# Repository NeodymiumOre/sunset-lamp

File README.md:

# SunsetLamp
Alarm clock simulating sunrise.

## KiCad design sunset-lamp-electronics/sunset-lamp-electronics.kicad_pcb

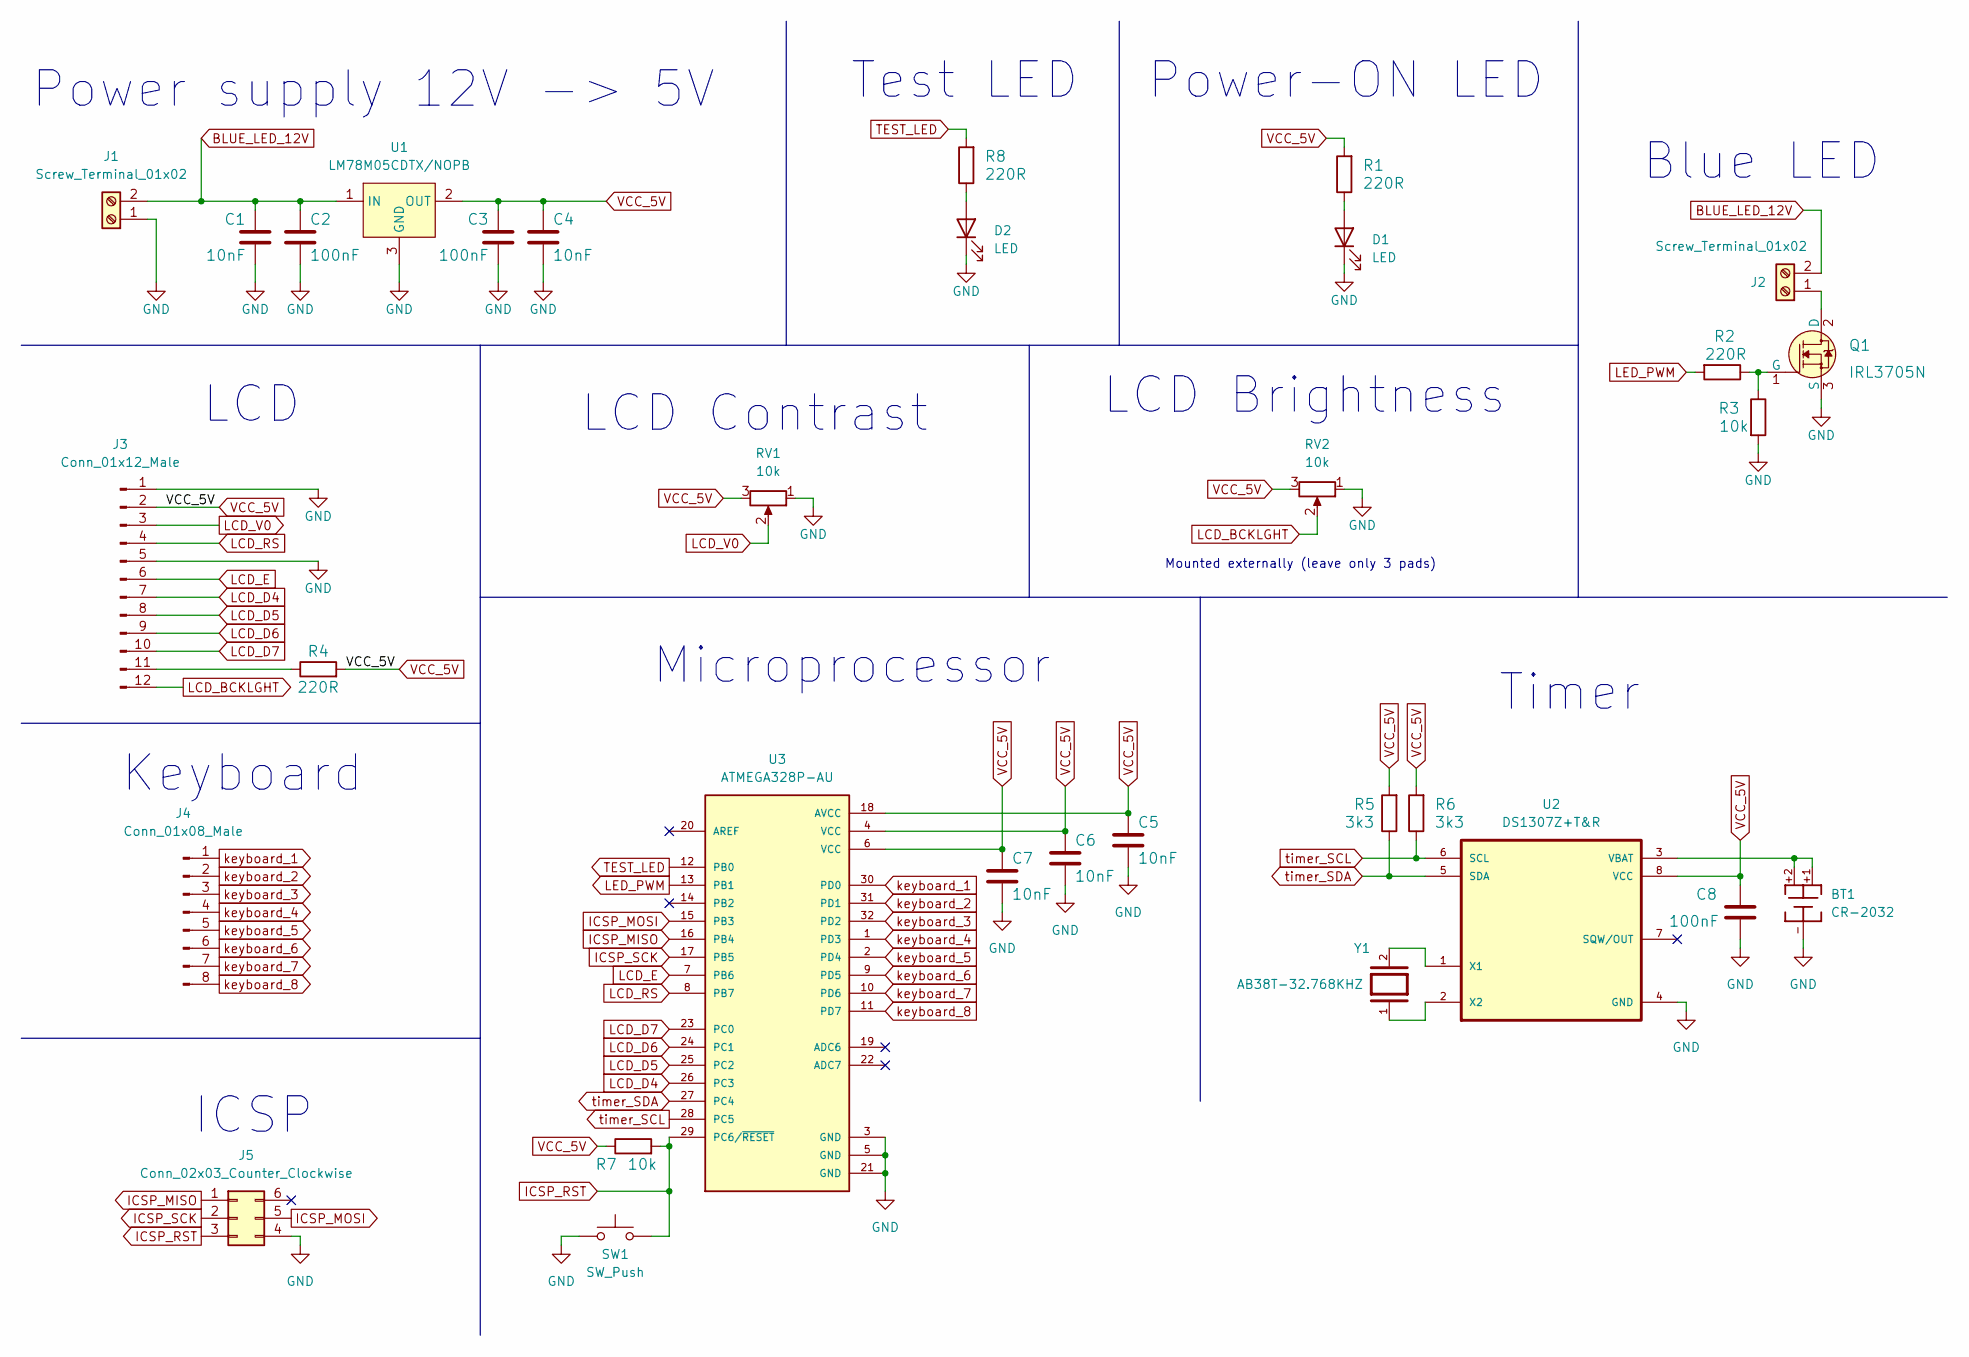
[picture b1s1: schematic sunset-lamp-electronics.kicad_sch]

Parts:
BT1: CR-2032; BAT_CR2032
C1, C4, C5, C6, C7: 10nF; 0402-cap
C2, C3, C8: 100nF; 0402-cap
D1, D2: LED; LED_0805_2012Metric_Pad1.15x1.40mm_HandSolder
J1, J2: Screw_Terminal_01x02; TerminalBlock_Altech_AK300-2_P5.00mm
J3: Conn_01x12_Male; PinHeader_1x12_P2.54mm_Vertical
J4: Conn_01x08_Male; PinHeader_1x08_P2.54mm_Vertical
J5: Conn_02x03_Counter_Clockwise; PinHeader_2x03_P2.54mm_Vertical
Q1: IRL3705N; TO-220
R1, R2, R4, R8: 220R; 0402-res
R3, R7: 10k; 0402-res
R5, R6: 3k3; 0402-res
RV1: 10k; TrimmPotentiometer
RV2: 10k; PinHeader_1x03_P2.54mm_Vertical
SW1: SW_Push; SW_PUSH_6mm_H5mm
U1: LM78M05CDTX/NOPB; TO-252-DPAK
U2: DS1307Z+T&R; SOIC-8
U3: ATMEGA328P-AU; TQFP-32
Y1: AB38T-32.768KHZ; XTAL_AB38T-32.768KHZ

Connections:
BLUE_LED_12V: C1.1, C2.1, J1.2, J2.2, U1.1 (IN)
GND: BT1.-, C1.2, C2.2, C3.2, C4.2, C5.2, C6.2, C7.2, C8.2, D1.1 (K), D2.1 (K), J1.1, J3.1, J3.5, J5.4, Q1.3 (S), R3.2, RV1.1, RV2.1, SW1.1, U1.3 (GND), U2.4 (GND), U3.3 (GND), U3.5 (GND), U3.21 (GND)
ICSP_MISO: J5.1, U3.16 (PB4)
ICSP_MOSI: J5.5, U3.15 (PB3)
ICSP_RST: J5.3, R7.2, SW1.2, U3.29 (PC6/~RESET)
ICSP_SCK: J5.2, U3.17 (PB5)
LCD_BCKLGHT: J3.12, RV2.2
LCD_D4: J3.7, U3.26 (PC3)
LCD_D5: J3.8, U3.25 (PC2)
LCD_D6: J3.9, U3.24 (PC1)
LCD_D7: J3.10, U3.23 (PC0)
LCD_E: J3.6, U3.7 (PB6)
LCD_RS: J3.4, U3.8 (PB7)
LCD_V0: J3.3, RV1.2
LED_PWM: R2.2, U3.13 (PB1)
unnamed: BT1.+1, BT1.+2, U2.3 (VBAT)
unnamed: D1.2 (A), R1.1
unnamed: D2.2 (A), R8.1
unnamed: J2.1, Q1.2 (D)
unnamed: J3.11, R4.1
unnamed: Q1.1 (G), R2.1, R3.1
unnamed: U2.1 (X1), Y1.2
unnamed: U2.2 (X2), Y1.1
TEST_LED: R8.2, U3.12 (PB0)
VCC_5V: C3.1, C4.1, C5.1, C6.1, C7.1, C8.1, J3.2, R1.2, R4.2, R5.2, R6.2, R7.1, RV1.3, RV2.3, U1.2 (OUT), U2.8 (VCC), U3.4 (VCC), U3.6 (VCC), U3.18 (AVCC)
keyboard_1: J4.1, U3.30 (PD0)
keyboard_2: J4.2, U3.31 (PD1)
keyboard_3: J4.3, U3.32 (PD2)
keyboard_4: J4.4, U3.1 (PD3)
keyboard_5: J4.5, U3.2 (PD4)
keyboard_6: J4.6, U3.9 (PD5)
keyboard_7: J4.7, U3.10 (PD6)
keyboard_8: J4.8, U3.11 (PD7)
timer_SCL: R6.1, U2.6 (SCL), U3.28 (PC5)
timer_SDA: R5.1, U2.5 (SDA), U3.27 (PC4)

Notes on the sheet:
LCD Brightness
Timer
Keyboard
LCD
LCD Contrast
ICSP
Test LED
Power supply 12V -> 5V
Power-ON LED
Microprocessor
Blue LED
Mounted externally (leave only 3 pads)

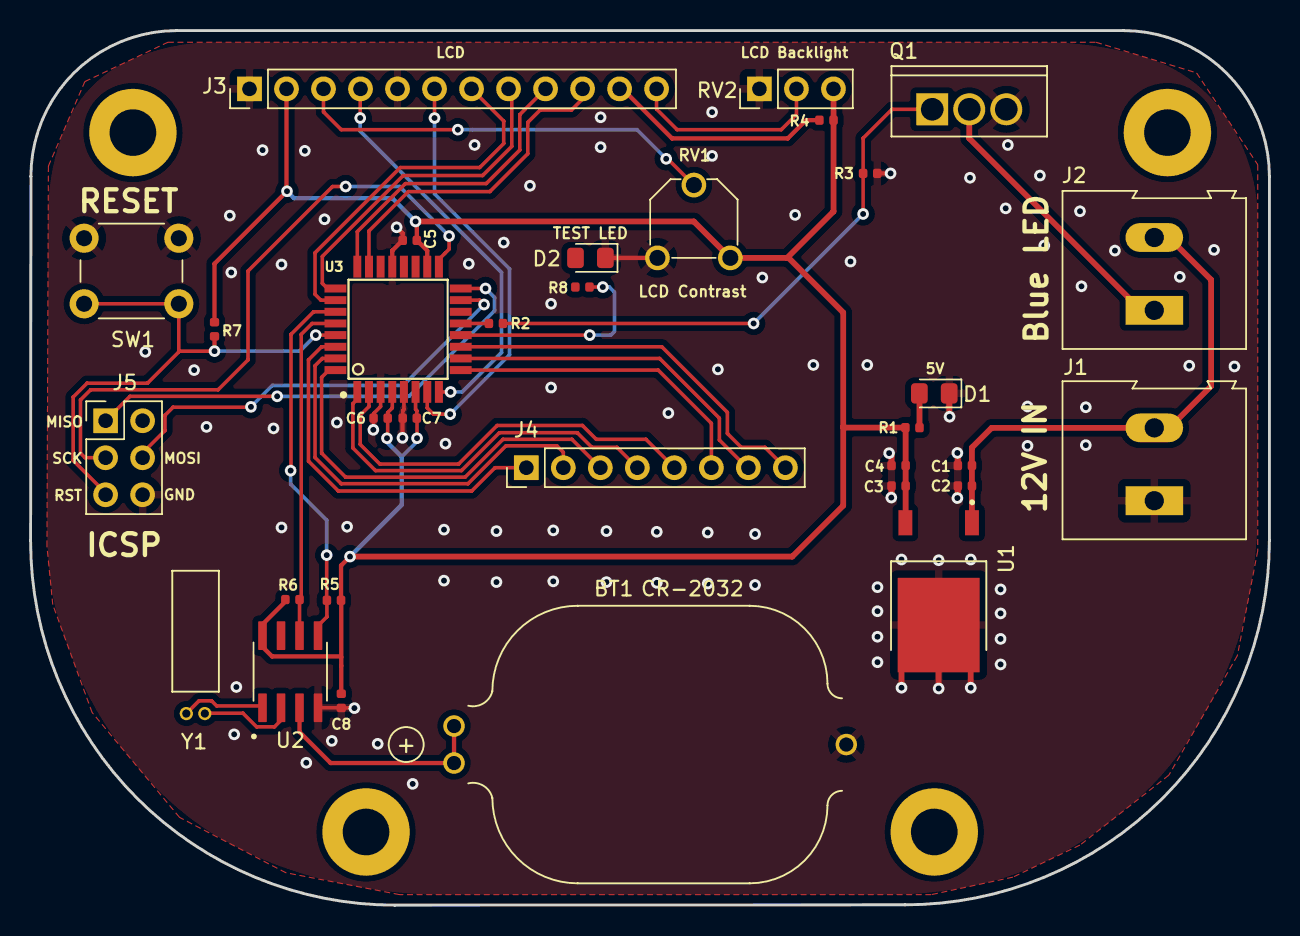
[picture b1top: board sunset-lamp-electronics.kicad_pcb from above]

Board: 2 copper layers, 85.0 x 60.0 mm, 32 parts (0 on the bottom side), 35 nets.

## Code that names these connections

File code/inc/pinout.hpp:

#include "pins_arduino.h"

// general pins
#define TEST_LED PIN_PB0
#define LED_PWM PIN_PB1
#define SOFT_RESET PIN_PC6

// LCD pins
#define LCD_E PIN_PB6
#define LCD_RS PIN_PB7
#define LCD_D7 PIN_PC0
#define LCD_D6 PIN_PC1
#define LCD_D5 PIN_PC2
#define LCD_D4 PIN_PC3

// KEYBOARD pins
#define ROW_1 PIN_PD0
#define ROW_2 PIN_PD1
#define ROW_3 PIN_PD2
#define ROW_4 PIN_PD3
#define COL_1 PIN_PD4
#define COL_2 PIN_PD5
#define COL_3 PIN_PD6
#define COL_4 PIN_PD7

// TIMER pins
#define TIMER_SDA PIN_PC4
#define TIMER_SCL PIN_PC5

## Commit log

2022-05-06 Code arduino test
2022-05-06 Working LCD test code
2022-05-06 Adding scheduler on millis() and led operated with button
2022-05-06 Started working on time table. Won't compile because of .h file.
2022-05-08 Adding RTC working code example. Now all eectronics is completed.
2022-12-10 Renamed directory
2022-12-11 Added electronics schematic
2022-12-11 Finished schematics and added footprints to all components
2022-12-11 Corrected R and C symbols and performed ERC
2022-12-11 Created PCB layout and resolved DRC errors
2022-12-20 Added test LED and gitignore file
2023-01-01 Added top copper layer, vias and corrected paths
2023-03-16 Updated schemat and pcb layout
2023-03-29 Added code test for blinking status LED
2024-12-27 Kicad dump
